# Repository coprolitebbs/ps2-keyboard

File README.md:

# ps2-keyboard
Самодельная клавиатура с интерфейсом ps/2.
Собрана на Attiny2313A и сдвиговых регистрах 74HC595 и 74HC165.

Прошивка Attiny базируется на библиотеке [ps2dev](https://github.com/Harvie/ps2dev)

Простое описание данных для протокола [PS/2](https://marsohod.org/11-blog/57-ps2proto).

Если что-то не работает, попробуйте старую прошивку из моей же статьи на хабре:
https://habr.com/ru/articles/693784/
Например, эмулятор PS/2 клавиатуры для Спектрума, почему-то, не заводится с последней версией прошивки, но, завелся с версией из статьи.
Собирали на стриме здесь: https://www.youtube.com/watch?v=hVR3ve-gX_8

Прошивка компилируется средой Arduino IDE,

Прошивается с помощью progisp172 программатором через порт "РПрог" для программирования на плате клавиатуры,

Fuse-биты для Attiny2313A: 
Low: E2, High: DF, Ext: FF, Lock: FF

**Имейте ввиду, клавиатура не настраивается под ваш PC или контроллер автоматически,
придется играться с таймингами в исходнике.**

**Для PC используйте значения:**
```
 #define BYTEWAIT 1000
 #define CLK_FULL 40 
 #define CLK_HALF 20
 #define TIMEOUT 30
```

**Для работы с esp32 и библиотекой FabGL используйте**
```
 #define BYTEWAIT 500
 #define CLK_FULL 10 
 #define CLK_HALF 5
 #define TIMEOUT 50
```

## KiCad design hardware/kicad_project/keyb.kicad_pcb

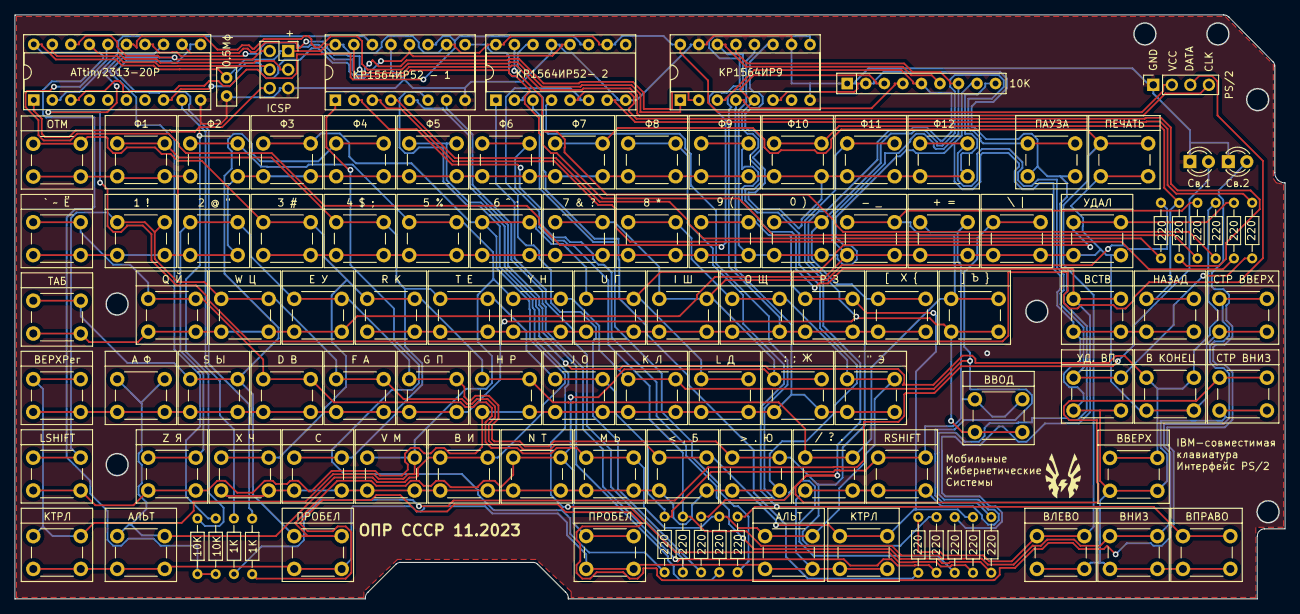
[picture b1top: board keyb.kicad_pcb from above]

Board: 2 copper layers, 173.9 x 79.9 mm, 114 parts (0 on the bottom side), 59 nets.

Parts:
C1: 0.5Mф; C_Disc_D5.0mm_W2.5mm_P2.50mm
D1: Св.1; LED_D3.0mm
D2: Св.2; LED_D3.0mm
J1: PS/2; PinSocket_1x04_P2.54mm_Vertical
J2: ICSP; PinSocket_2x03_P2.54mm_Vertical_ICSP
R1, R4: 10K; R_Axial_DIN0204_L3.6mm_D1.6mm_P7.62mm_Horizontal
R2, R3: 1K; R_Axial_DIN0204_L3.6mm_D1.6mm_P7.62mm_Horizontal
R5, R6, R7, R8, R9, R10, R11, R12, R13, R14, R15, R16, R17, R18, R19, R20: 220; R_Axial_DIN0204_L3.6mm_D1.6mm_P7.62mm_Horizontal
RN1: 10K; R_Array_SIP9
SW1: ОТМ; SW_PUSH_KEYB_6mm_H4.3mm
SW2: Ф1; SW_PUSH_KEYB_6mm_H4.3mm
SW3: Ф2; SW_PUSH_KEYB_6mm_H4.3mm
SW4: Ф3; SW_PUSH_KEYB_6mm_H4.3mm
SW5: Ф4; SW_PUSH_KEYB_6mm_H4.3mm
SW6: ` ~ Ё; SW_PUSH_KEYB_6mm_H4.3mm
SW7: 1 !; SW_PUSH_KEYB_6mm_H4.3mm
SW8: 2 @ "; SW_PUSH_KEYB_6mm_H4.3mm
SW9: Ф5; SW_PUSH_KEYB_6mm_H4.3mm
SW10: Ф6; SW_PUSH_KEYB_6mm_H4.3mm
SW11: Ф7; SW_PUSH_KEYB_6mm_H4.3mm
SW12: Ф8; SW_PUSH_KEYB_6mm_H4.3mm
SW13: Ф9; SW_PUSH_KEYB_6mm_H4.3mm
SW14: Ф10; SW_PUSH_KEYB_6mm_H4.3mm
SW15: Ф11; SW_PUSH_KEYB_6mm_H4.3mm
SW16: Ф12; SW_PUSH_KEYB_6mm_H4.3mm
SW17: 3 #; SW_PUSH_KEYB_6mm_H4.3mm
SW18: 4 $ ;; SW_PUSH_KEYB_6mm_H4.3mm
SW19: 5 %; SW_PUSH_KEYB_6mm_H4.3mm
SW20: 6 ^ :; SW_PUSH_KEYB_6mm_H4.3mm
SW21: 7 & ?; SW_PUSH_KEYB_6mm_H4.3mm
SW22: 8 *; SW_PUSH_KEYB_6mm_H4.3mm
SW23: 9 (; SW_PUSH_KEYB_6mm_H4.3mm
SW24: 0 ); SW_PUSH_KEYB_6mm_H4.3mm
SW25: ВВЕРХ; SW_PUSH_KEYB_6mm_H4.3mm
SW26: ВНИЗ; SW_PUSH_KEYB_6mm_H4.3mm
SW27: ВЛЕВО; SW_PUSH_KEYB_6mm_H4.3mm
SW28: ВПРАВО; SW_PUSH_KEYB_6mm_H4.3mm
SW29: ВСТВ; SW_PUSH_KEYB_6mm_H4.3mm
SW30: НАЗАД; SW_PUSH_KEYB_6mm_H4.3mm
SW31: СТР ВНИЗ; SW_PUSH_KEYB_6mm_H4.3mm
SW32: УД. ВП.; SW_PUSH_KEYB_6mm_H4.3mm
SW33: - _; SW_PUSH_KEYB_6mm_H4.3mm
SW34: + =; SW_PUSH_KEYB_6mm_H4.3mm
SW35: \ |; SW_PUSH_KEYB_6mm_H4.3mm
SW36: УДАЛ; SW_PUSH_KEYB_6mm_H4.3mm
SW37: ТАБ; SW_PUSH_KEYB_6mm_H4.3mm
SW38: Q Й; SW_PUSH_KEYB_6mm_H4.3mm
SW39: W Ц; SW_PUSH_KEYB_6mm_H4.3mm
SW40: E У; SW_PUSH_KEYB_6mm_H4.3mm
SW41: В КОНЕЦ; SW_PUSH_KEYB_6mm_H4.3mm
SW42: СТР ВВЕРХ; SW_PUSH_KEYB_6mm_H4.3mm
SW43: ПЕЧАТЬ; SW_PUSH_KEYB_6mm_H4.3mm
SW44: R К; SW_PUSH_KEYB_6mm_H4.3mm
SW45: T Е; SW_PUSH_KEYB_6mm_H4.3mm
SW46: Y Н; SW_PUSH_KEYB_6mm_H4.3mm
SW47: U Г; SW_PUSH_KEYB_6mm_H4.3mm
SW48: I Ш; SW_PUSH_KEYB_6mm_H4.3mm
SW49: O Щ; SW_PUSH_KEYB_6mm_H4.3mm
SW50: P З; SW_PUSH_KEYB_6mm_H4.3mm
SW51: [ X {; SW_PUSH_KEYB_6mm_H4.3mm
SW52: ] Ъ }; SW_PUSH_KEYB_6mm_H4.3mm
SW53: ВВОД; SW_PUSH_KEYB_6mm_H4.3mm
SW54: ВЕРХРег; SW_PUSH_KEYB_6mm_H4.3mm
SW55: A Ф; SW_PUSH_KEYB_6mm_H4.3mm
SW56: S Ы; SW_PUSH_KEYB_6mm_H4.3mm
SW57: D В; SW_PUSH_KEYB_6mm_H4.3mm
SW58: F А; SW_PUSH_KEYB_6mm_H4.3mm
SW59: G П; SW_PUSH_KEYB_6mm_H4.3mm
SW60: H Р; SW_PUSH_KEYB_6mm_H4.3mm
SW61: J О; SW_PUSH_KEYB_6mm_H4.3mm
SW62: K Л; SW_PUSH_KEYB_6mm_H4.3mm
SW63: L Д; SW_PUSH_KEYB_6mm_H4.3mm
SW64: : ; Ж; SW_PUSH_KEYB_6mm_H4.3mm
SW65: ' " Э; SW_PUSH_KEYB_6mm_H4.3mm
SW66: LSHIFT; SW_PUSH_KEYB_6mm_H4.3mm
SW67: Z Я; SW_PUSH_KEYB_6mm_H4.3mm
SW68: X Ч; SW_PUSH_KEYB_6mm_H4.3mm
SW69: C; SW_PUSH_KEYB_6mm_H4.3mm
SW70: V М; SW_PUSH_KEYB_6mm_H4.3mm
SW71: B И; SW_PUSH_KEYB_6mm_H4.3mm
SW72: N Т; SW_PUSH_KEYB_6mm_H4.3mm
SW73: M Ь; SW_PUSH_KEYB_6mm_H4.3mm
SW74: < , Б; SW_PUSH_KEYB_6mm_H4.3mm
SW75: > . Ю; SW_PUSH_KEYB_6mm_H4.3mm
SW76: / ? .; SW_PUSH_KEYB_6mm_H4.3mm
SW77: RSHIFT; SW_PUSH_KEYB_6mm_H4.3mm
SW78, SW82: КТРЛ; SW_PUSH_KEYB_6mm_H4.3mm
SW79, SW81: АЛЬТ; SW_PUSH_KEYB_6mm_H4.3mm
SW80, SW84: ПРОБЕЛ; SW_PUSH_KEYB_6mm_H4.3mm
SW83: ПАУЗА; SW_PUSH_KEYB_6mm_H4.3mm
U1: ATtiny2313-20P; DIP-20_W7.62mm_Socket
U2: KP1564ИP52 - 1; DIP-16_W7.62mm_Socket
U3: KP1564ИP52- 2; DIP-16_W7.62mm_Socket
U4: KP1564ИP9; DIP-16_W7.62mm_Socket

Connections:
+5V: C1.2, J1.2, J2.1 (VDD), R1.1, R4.1, U1.20 (VCC), U2.10 (~SRCLR), U2.16 (VCC), U3.10 (~SRCLR), U3.16 (VCC), U4.16 (VCC)
CP_clk: U1.14 (PB2), U4.2 (CP)
D0_165: RN1.9 (R8), SW1.2, SW2.2, SW3.2, SW4.2, SW5.2, SW6.2, SW7.2, SW8.2, SW9.2, SW10.2, SW11.2, SW12.2, SW13.2, SW14.2, SW15.2, SW16.2, U4.11 (D0)
D1_165: RN1.8 (R7), SW17.2, SW18.2, SW19.2, SW20.2, SW21.2, SW22.2, SW23.2, SW24.2, SW25.2, SW26.2, SW27.2, SW28.2, SW29.2, SW30.2, SW31.2, SW32.2, U4.12 (D1)
D2_165: RN1.7 (R6), SW33.2, SW34.2, SW35.2, SW36.2, SW37.2, SW38.2, SW39.2, SW40.2, SW41.2, SW42.2, SW43.2, U4.13 (D2)
D3_165: RN1.6 (R5), SW44.2, SW45.2, SW46.2, SW47.2, SW48.2, SW49.2, SW50.2, SW51.2, U4.14 (D3)
D4_165: RN1.5 (R4), SW52.2, SW53.2, SW54.2, SW55.2, SW56.2, SW57.2, SW58.2, SW59.2, U4.3 (D4)
D5_165: RN1.4 (R3), SW60.2, SW61.2, SW62.2, SW63.2, SW64.2, SW65.2, SW66.2, SW67.2, U4.4 (D5)
D6_165: RN1.3 (R2), SW68.2, SW69.2, SW70.2, SW71.2, SW72.2, SW73.2, SW74.2, SW75.2, U4.5 (D6)
D7_165: RN1.2 (R1), SW76.2, SW77.2, SW78.2, SW79.2, SW80.2, SW81.2, SW82.2, SW83.2, SW84.2, U4.6 (D7)
DATA: U1.2 (PD0), U2.14 (SER)
DATA_C: U1.3 (PD1), U2.11 (SRCLK), U3.11 (SRCLK)
GND: C1.1, D1.1 (K), D2.1 (K), J1.1, J2.5 (GND), RN1.1 (common), U1.10 (GND), U2.8 (GND), U2.13 (~OE), U3.8 (GND), U3.13 (~OE), U4.8 (GND), U4.10 (DS), U4.15 (~CE)
KL0_595: R5.2, SW1.1, SW17.1, SW33.1, SW44.1, SW52.1, SW60.1, SW68.1, SW76.1
KL1_595: R17.2, SW2.1, SW18.1, SW34.1, SW45.1, SW53.1, SW61.1, SW69.1, SW77.1
KL2_595: R6.2, SW3.1, SW19.1, SW35.1, SW46.1, SW54.1, SW62.1, SW70.1, SW78.1
KL3_595: R18.2, SW4.1, SW20.1, SW36.1, SW47.1, SW55.1, SW63.1, SW71.1, SW79.1
KL4_595: R7.2, SW5.1, SW21.1, SW37.1, SW48.1, SW56.1, SW64.1, SW72.1, SW80.1, SW84.1
KL5_595: R19.2, SW6.1, SW22.1, SW38.1, SW49.1, SW57.1, SW65.1, SW73.1, SW81.1
KL6_595: R8.2, SW7.1, SW23.1, SW39.1, SW50.1, SW58.1, SW66.1, SW74.1, SW82.1
KL7_595: R20.2, SW8.1, SW24.1, SW40.1, SW51.1, SW59.1, SW67.1, SW75.1, SW83.1
KL8_595: R9.2, SW9.1, SW25.1, SW41.1
KL9_595: R13.2, SW10.1, SW26.1, SW42.1
KL10_595: R10.2, SW11.1, SW27.1, SW43.1
KL11_595: R14.2, SW12.1, SW28.1
KL12_595: R11.2, SW13.1, SW29.1
KL13_595: R15.2, SW14.1, SW30.1
KL14_595: R12.2, SW15.1, SW31.1
KL15_595: R16.2, SW16.1, SW32.1
LED_1: R2.2, U1.9 (PD5)
LED_2: R3.2, U1.11 (PD6)
MISO: J2.2 (MISO), R4.2, U1.18 (PB6)
MOSI: J2.3 (MOSI), U1.17 (PB5)
unnamed: D1.2 (A), R2.1
unnamed: D2.2 (A), R3.1
unnamed: R5.1, U2.15 (QA)
unnamed: R17.1, U2.1 (QB)
unnamed: R6.1, U2.2 (QC)
unnamed: R18.1, U2.3 (QD)
unnamed: R7.1, U2.4 (QE)
unnamed: R19.1, U2.5 (QF)
unnamed: R8.1, U2.6 (QG)
unnamed: U2.9 (QH'), U3.14 (SER)
unnamed: R20.1, U2.7 (QH)
unnamed: R9.1, U3.15 (QA)
unnamed: R13.1, U3.1 (QB)
unnamed: R10.1, U3.2 (QC)
unnamed: R14.1, U3.3 (QD)
unnamed: R11.1, U3.4 (QE)
unnamed: R15.1, U3.5 (QF)
unnamed: R12.1, U3.6 (QG)
unnamed: R16.1, U3.7 (QH)
OUT_C: U1.8 (PD4), U2.12 (RCLK), U3.12 (RCLK)
PCLK: J1.4, U1.12 (PB0)
PDATA: J1.3, U1.13 (PB1)
PL_di: U1.15 (PB3), U4.1 (~PL)
RST: J2.6 (RST), R1.2, U1.1 (PA2/~RESET)
SCK: J2.4 (CSK), U1.19 (PB7)
SO: U1.16 (PB4), U4.9 (Q7)

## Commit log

2023-08-12 Update ps2-keyb.ino
    Чуть доработано для поддержки нормального ресета по коду, иначе некоторые библиотеки типа FabGL не работали с клавиатурой нормально.
2023-11-15 Iteration 2
